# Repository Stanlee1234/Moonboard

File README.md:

# Moonboard

Moonboard is a Tamagotchi-style game played on a custom PCB.
The idea is simple: look after your moon every day and help it move through its
eight phases. I wanted it to feel like a small object you could keep on your desk,
pick up, and play with for a minute.

I made this project for [Hack Club Half Life](https://halflife.hackclub.com/?ref=3159).

## Try it without the board

I currently don't have the physical board, so no demos. I do have a firmware simulator. To get there,
open [`Firmware/simulator/index.html`](Firmware/simulator/index.html) and you can try out most features of my console!

Use `Q` / `W` / `E` for the top row and `A` / `S` / `D` for the bottom row, or just
click the buttons. The simulator is intentionally simple, but it makes it much
easier to try ideas without constantly flashing the board.

## What it can do

- Show all eight moon phases on the OLED
- Let you move around with a six-key matrix
- Use the rotary potentiometer for game input
- React to tilting and shaking through the MPU6050
- Read temperature and humidity from the DHT11
- Run on a XIAO ESP32-C3, with fallbacks for testing without every sensor connected

## The parts

| Part | Role |
| --- | --- |
| Part | What I’m using it for |
| --- | --- |
| XIAO ESP32-C3 | Running the game |
| 128x64 SSD1306 OLED | Showing the moon and menus over I2C |
| 6 mechanical keys | The 2x3 game controls |
| EC11 rotary encoder | Navigation and extra game input |
| MPU6050 | Tilt and shake interactions |
| DHT11 | Temperature and humidity experiments |

See [`BOM.md`](BOM.md) for the complete parts list and [`KiCAD/`](KiCAD/) for
the schematic, PCB, and manufacturing exports.

## Images

| Schematic | PCB |
| :---: | :---: |
|  |  |

## Renders

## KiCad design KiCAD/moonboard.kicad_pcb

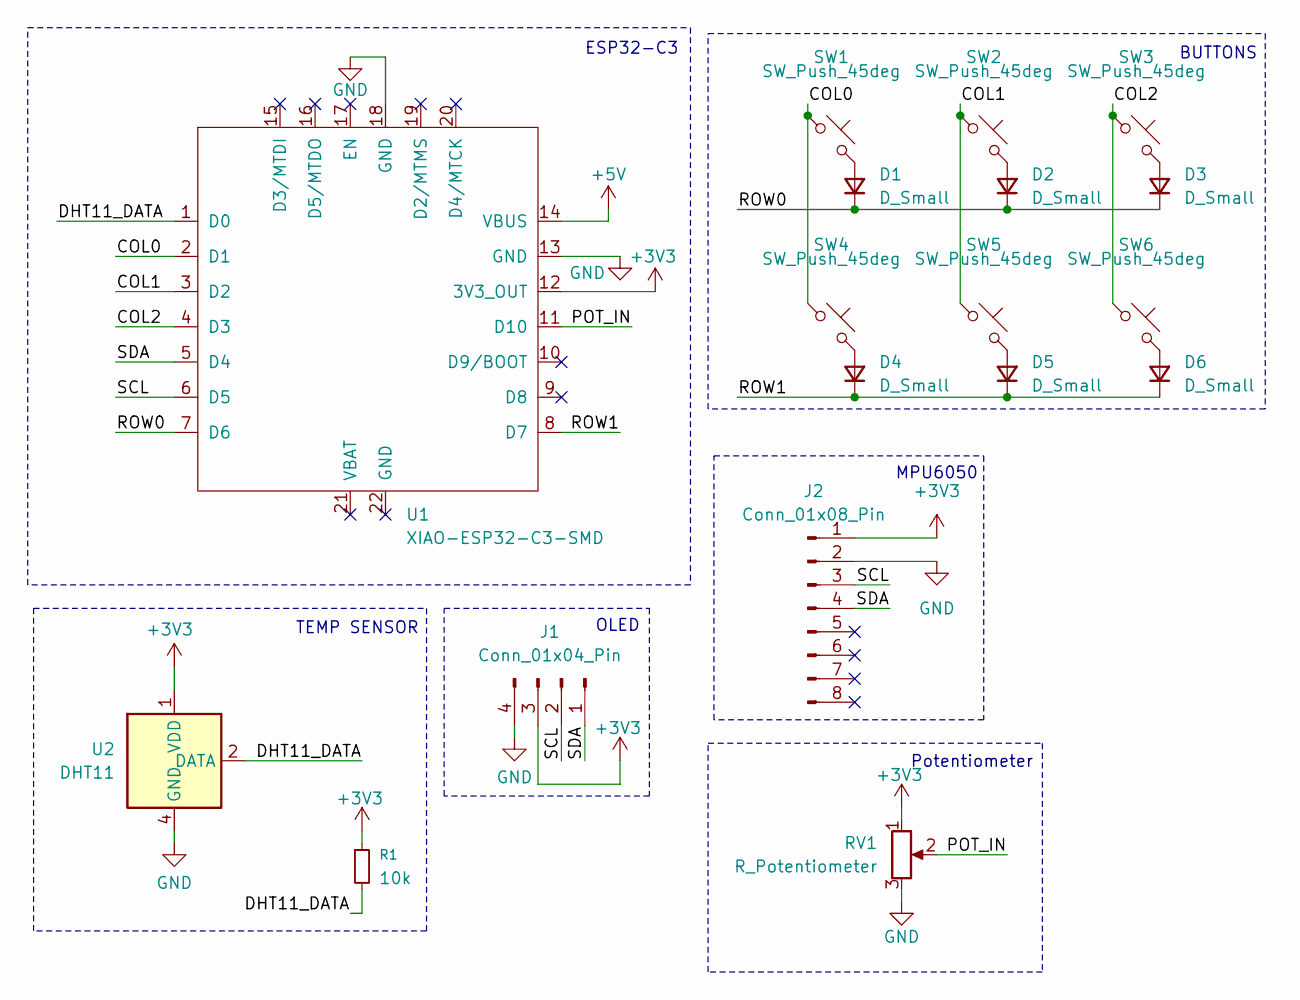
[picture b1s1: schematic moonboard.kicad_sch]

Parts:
D1, D2, D3, D4, D5, D6: D_Small; D_SOD-123
J1: Conn_01x04_Pin; OLED_SSD1306_I2C_0.96
J2: Conn_01x08_Pin; MODULE_GY-521
R1: 10k; R_0805_2012Metric
RV1: R_Potentiometer; RotaryEncoder_Alps_EC11E-Switch_Vertical_H20mm
SW1, SW2, SW3, SW4, SW5, SW6: SW_Push_45deg; Hotswap_MX_1.00u
U1: XIAO-ESP32-C3-SMD
U2: DHT11; Aosong_DHT11_5.5x12.0_P2.54mm

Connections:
+3V3: J1.3, J2.1, R1.1, RV1.1, U1.12 (3V3_OUT), U2.1 (VDD)
+5V: U1.14 (VBUS)
/COL0: SW1.1, SW4.1, U1.2 (D1)
/COL1: SW2.1, SW5.1, U1.3 (D2)
/COL2: SW3.1, SW6.1, U1.4 (D3)
/DHT11_DATA: R1.2, U1.1 (D0), U2.2 (DATA)
/POT_IN: RV1.2, U1.11 (D10)
/ROW0: D1.1 (K), D2.1 (K), D3.1 (K), U1.7 (D6)
/ROW1: D4.1 (K), D5.1 (K), D6.1 (K), U1.8 (D7)
/SCL: J1.2, J2.3, U1.6 (D5)
/SDA: J1.1, J2.4, U1.5 (D4)
GND: J1.4, J2.2, RV1.3, U1.13 (GND), U1.18 (GND), U2.4 (GND)
unnamed: D1.2 (A), SW1.2
unnamed: D2.2 (A), SW2.2
unnamed: D3.2 (A), SW3.2
unnamed: D4.2 (A), SW4.2
unnamed: D5.2 (A), SW5.2
unnamed: D6.2 (A), SW6.2

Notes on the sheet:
Potentiometer
TEMP SENSOR
ESP32-C3
OLED
BUTTONS
MPU6050

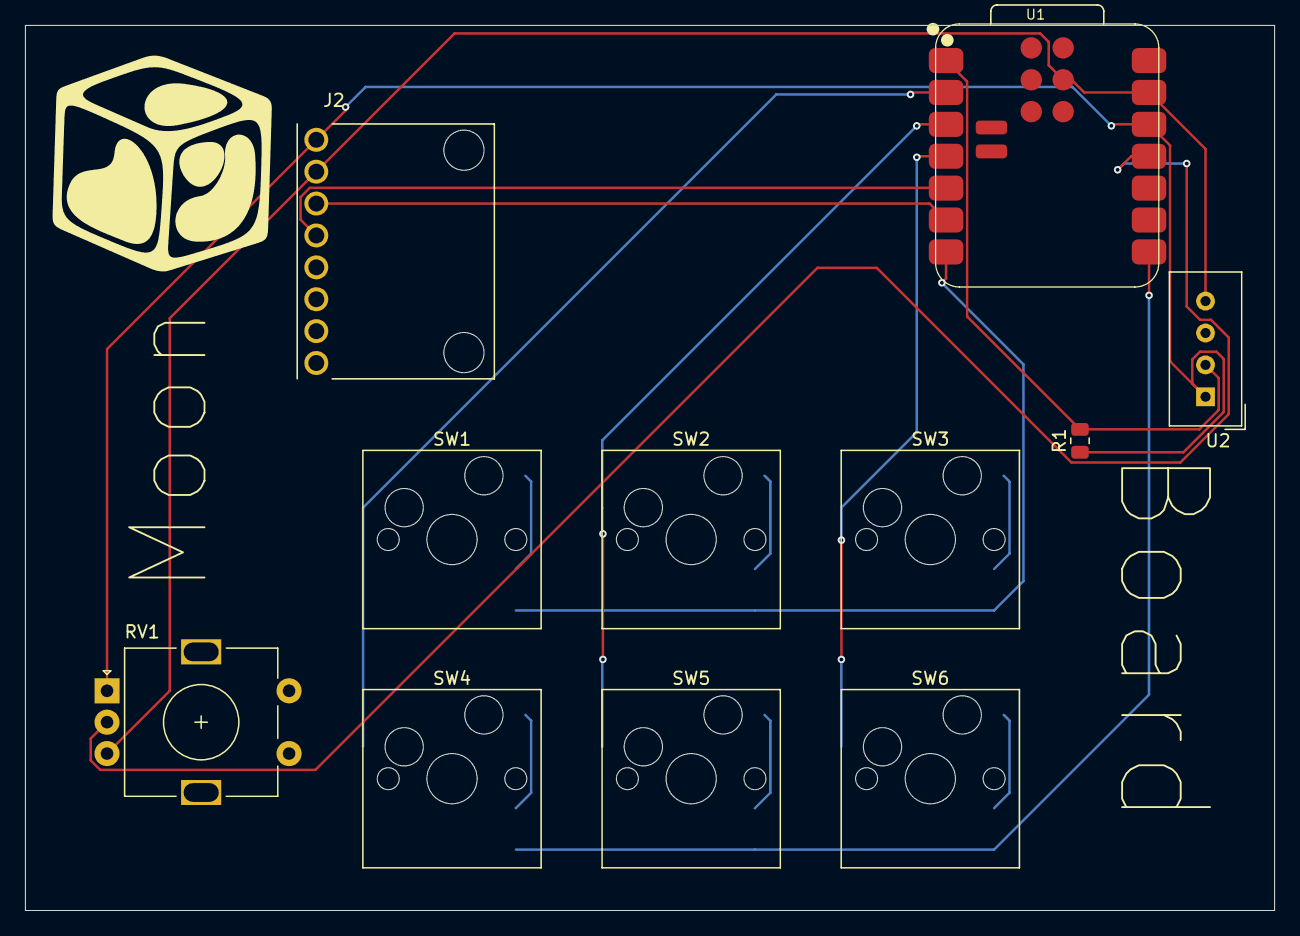
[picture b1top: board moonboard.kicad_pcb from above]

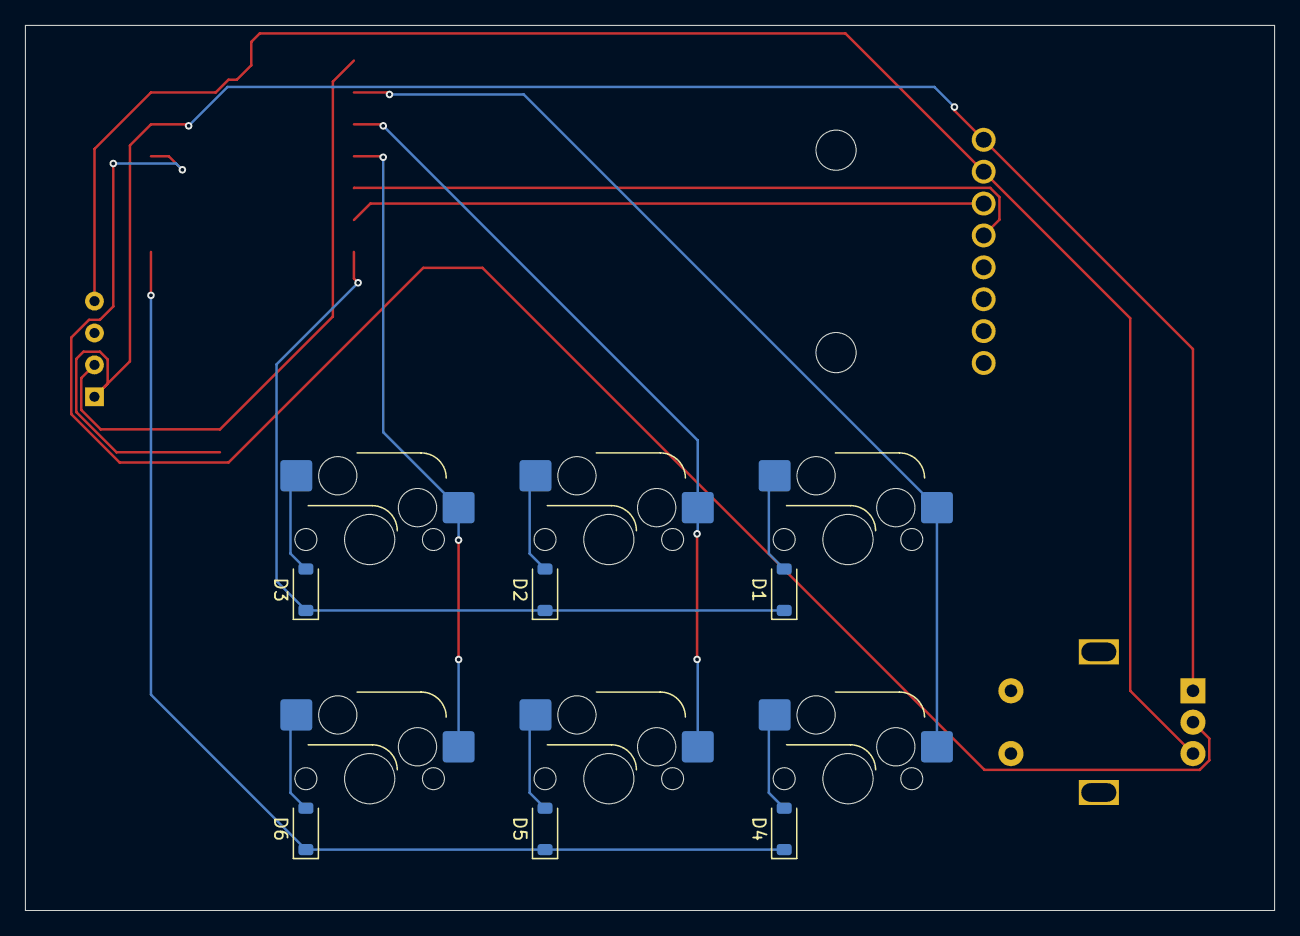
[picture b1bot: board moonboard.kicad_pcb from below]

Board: 2 copper layers, 99.5 x 70.5 mm, 17 parts (6 on the bottom side), 17 nets.

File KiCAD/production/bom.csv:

Designator,Footprint,Quantity,Value,LCSC Part #
"D1, D2, D3, D4, D5, D6",D_SOD-123,6,D_Small,
J1,OLED_SSD1306_I2C_0.96,1,Conn_01x04_Pin,
J2,MODULE_GY-521,1,Conn_01x08_Pin,
R1,0805,1,10k,
RV1,RotaryEncoder_Alps_EC11E-Switch_Vertical_H20mm,1,R_Potentiometer,
"SW1, SW2, SW3, SW4, SW5, SW6",Hotswap_MX_1.00u,6,SW_Push_45deg,
U1,XIAO-ESP32-C3-SMD,1,XIAO-ESP32-C3-SMD,
U2,Aosong_DHT11_5.5x12.0_P2.54mm,1,DHT11,
